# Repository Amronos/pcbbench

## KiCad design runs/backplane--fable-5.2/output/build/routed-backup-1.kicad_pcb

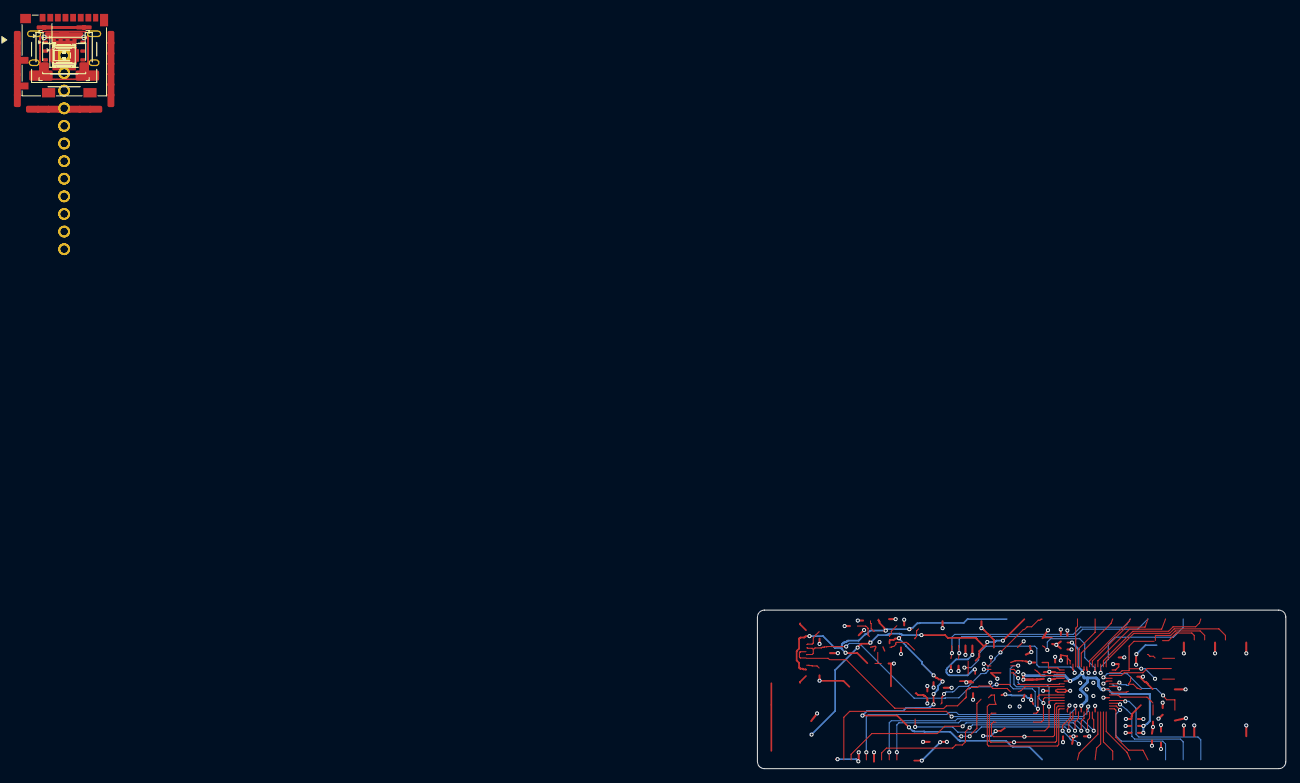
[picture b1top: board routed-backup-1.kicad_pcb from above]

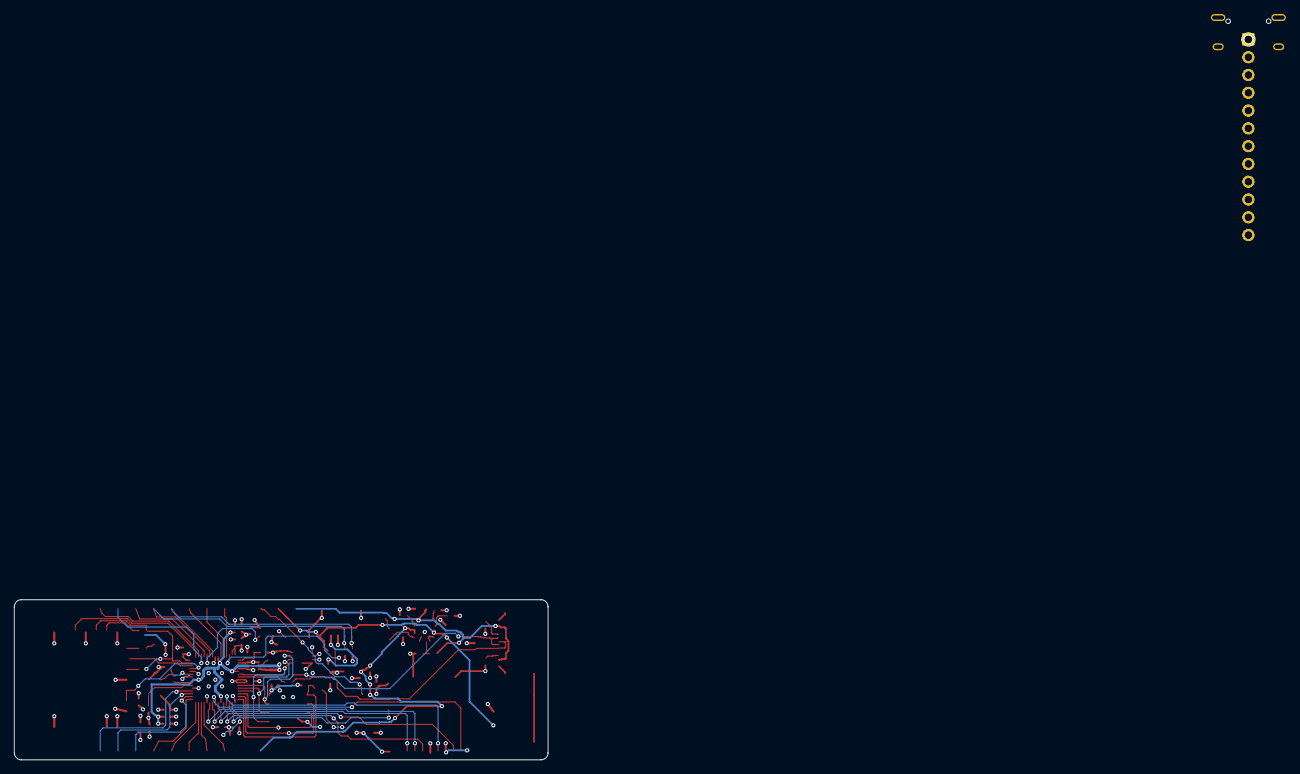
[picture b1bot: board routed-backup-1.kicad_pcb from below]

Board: 4 copper layers, 76.2 x 22.9 mm, 76 parts (3 on the bottom side), 68 nets.

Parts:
C1: 4.7uF; C_0603_1608Metric
C2, C3, C4, C28, C30: 10uF; C_0603_1608Metric
C5: 1uF; C_0402_1005Metric
C6, C7, C8, C9, C10, C11, C12, C13, C15, C16, C17, C18, C25, C26, C27, C29, C31, C32: 100nF; C_0402_1005Metric
C19, C20, C21: 4.7uF; C_0402_1005Metric
C23, C24: 15pF; C_0402_1005Metric
D1: WS2812B-2020; LED_WS2812B-2020_PLCC4_2.0x2.0mm
D2: ORANGE; LED_0603_1608Metric
D3: GREEN; LED_0603_1608Metric
J1: USB-C; USB_C_Receptacle_HRO_TYPE-C-31-M-12
J2: LiPo; JST_PH_S2B-PH-SM4-TB_1x02-1MP_P2.00mm_Horizontal
J3: Qwiic; JST_SH_SM04B-SRSS-TB_1x04-1MP_P1.00mm_Horizontal
J4: microSD; microSD_HC_Molex_104031-0811
J5: HDR_TOP; PinHeader_1x12_P2.54mm_Vertical
J6: HDR_BOT; PinHeader_1x12_P2.54mm_Vertical
L1: 3.3uH; L_Murata_DFE201610P
R1, R2: 5.1k; R_0402_1005Metric
R3, R4: 27R; R_0402_1005Metric
R5, R17, R19, R26: 10k; R_0402_1005Metric
R6: 1.5k; R_0402_1005Metric
R7: 3.0k; R_0402_1005Metric
R8, R11: 100k; R_0402_1005Metric
R9: 150k; R_0402_1005Metric
R10, R28, R29: 2.2k; R_0402_1005Metric
R12, R13: 200k; R_0402_1005Metric
R14: 33R; R_0402_1005Metric
R15, R18, R27: 1k; R_0402_1005Metric
R25: 470R; R_0402_1005Metric
SW1: BOOT; SW_SPST_B3U-1000P
SW2: RESET; SW_SPST_B3U-1000P
TP1: SWCLK; TestPoint_Pad_D1.0mm
TP2: SWDIO; TestPoint_Pad_D1.0mm
TP3: GND; TestPoint_Pad_D1.5mm
U1: RP2350A; QFN-60-1EP_7x7mm_P0.4mm_EP3.4x3.4mm
U2: W25Q128JVPIQ; WSON-8-1EP_6x5mm_P1.27mm_EP3.4x4.3mm
U3: APS6404L-3SQR-ZR; Winbond_USON-8-1EP_3x2mm_P0.5mm_EP0.2x1.6mm
U4: BQ24074RGTR; VQFN-16-1EP_3x3mm_P0.5mm_EP1.6x1.6mm
U5: TLV75733PDBVR; SOT-23-5
U6: USBLC6-2SC6; SOT-23-6
U7: RM2; RMC20452T
Y1: 12MHz; Crystal_SMD_3225-4Pin_3.2x2.5mm

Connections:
+1V1: C16.1, C17.1, C18.1, C21.1, L1.1, U1.6, U1.23, U1.39, U1.50
+3V3: C4.1, C7.1, C8.1, C9.1, C10.1, C11.1, C12.1, C13.1, C15.1, C19.1, C25.1, C26.1, C27.1, C28.1, C29.1, C30.1, C31.1, C32.1, D1.4, J3.2, J4.4, J6.1, R14.1, R17.1, R19.1, R28.1, R29.1, U1.1, U1.11, U1.20, U1.30, U1.38, U1.44, U1.45, U1.49, U1.53, U1.54, U2.8, U3.8, U5.5, U7.14, U7.16
/BAT_SENSE: C6.1, R12.2, R13.1, U1.43
/BOOT: R18.2, SW1.1
/CC1: J1.A5, R1.1
/CC2: J1.B5, R2.1
/CHG_A: D2.2, R10.2
/CHG_N: D2.1, U4.9
/EN: J5.3, R11.2, U5.3
/GP8: J6.5, U1.12
/GP9: J6.6, U1.13
/GP10: J6.7, U1.14
/GP11: J6.8, U1.15
/GP12: J6.9, U1.16
/GP13: J6.10, U1.17
/GP14: J6.11, U1.18
/GP15: J6.12, U1.19
/GP20: J5.12, U1.32
/GP21: J5.11, U1.33
/GP22: J5.10, U1.34
/GP26_A0: J5.7, U1.40
/GP27_A1: J5.6, U1.41
/GP28_A2: J5.5, U1.42
/ILIM: R6.1, U4.12
/ISET: R7.1, U4.16
/LED_A: D3.2, R27.2
/PSRAM_CS: R19.2, U1.2, U3.1
/QSPI_SCLK: U1.56, U2.6, U3.6
/QSPI_SD0: U1.57, U2.5, U3.5
/QSPI_SD1: U1.59, U2.2, U3.2
/QSPI_SD2: U1.58, U2.3, U3.3
/QSPI_SD3: U1.55, U2.7, U3.7
/QSPI_SS: R17.2, R18.1, U1.60, U2.1
/RGB_DIN: D1.3, U1.35
/RUN: SW2.1, U1.26
/SCL: J3.4, J5.8, R29.2, U1.37
/SDA: J3.3, J5.9, R28.2, U1.36
/SD_CD: J4.9, U1.3
/SD_CLK: J4.5, U1.4
/SD_CMD: J4.3, U1.5
/SD_D0: J4.7, U1.7
/SD_D1: J4.8, U1.8
/SD_D2: J4.1, U1.9
/SD_D3: J4.2, U1.10
/SWCLK: TP1.1, U1.24
/SWDIO: TP2.1, U1.25
/TS: R5.1, U4.1
/USB_DM: J1.A7, J1.B7, R4.1, U6.1, U6.6
/USB_DM_R: R4.2, U1.51
/USB_DP: J1.A6, J1.B6, R3.1, U6.3, U6.4
/USB_DP_R: R3.2, U1.52
/VBUS_DET: R8.2, R9.1, U4.6
/VREG_AVDD: C20.1, R14.2, U1.46
/VREG_LX: L1.2, U1.48
/WL_CLK: U1.31, U7.3
/WL_CS: U1.28, U7.9
/WL_D: R25.2, R26.1, U1.29, U7.5
/WL_DOUT: R25.1, U7.6
/WL_GPIO0: R27.1, U7.8
/WL_IRQ: R26.2, U7.10
/WL_ON: U1.27, U7.12, U7.13
/XIN: C23.1, U1.21, Y1.1
/XOUT: R15.1, U1.22
/XTAL_O: C24.1, R15.2, Y1.3
GND: C1.2, C2.2, C3.2, C4.2, C5.2, C6.2, C7.2, C8.2, C9.2, C10.2, C11.2, C12.2, C13.2, C15.2, C16.2, C17.2, C18.2, C19.2, C20.2, C21.2, C23.2, C24.2, C25.2, C26.2, C27.2, C28.2, C29.2, C30.2, C31.2, C32.2, D1.2, D3.1, J1.A1, J1.A12, J1.B1, J1.B12, J1.SH, J2.1, J2.MP, J3.1, J3.MP, J4.6, J4.10, J4.SH, J5.4, J6.2, J6.4, R1.2, R2.2, R5.2, R6.2, R7.2, R9.2, R13.2, SW1.2, SW2.2, TP3.1, U1.47, U1.61, U2.4, U2.9, U3.4, U3.9, U4.4, U4.5, U4.8, U4.17, U5.2, U6.2, U7.1, U7.4, U7.7, U7.11, U7.15, U7.21, Y1.2, Y1.4
VBAT: C3.1, J2.2, J5.2, R12.1, U4.2, U4.3
VBUS: C1.1, J1.A4, J1.A9, J1.B4, J1.B9, J5.1, R8.1, R10.1, U4.13, U6.5
VSYS: C2.1, C5.1, J6.3, R11.1, U4.10, U4.11, U5.1

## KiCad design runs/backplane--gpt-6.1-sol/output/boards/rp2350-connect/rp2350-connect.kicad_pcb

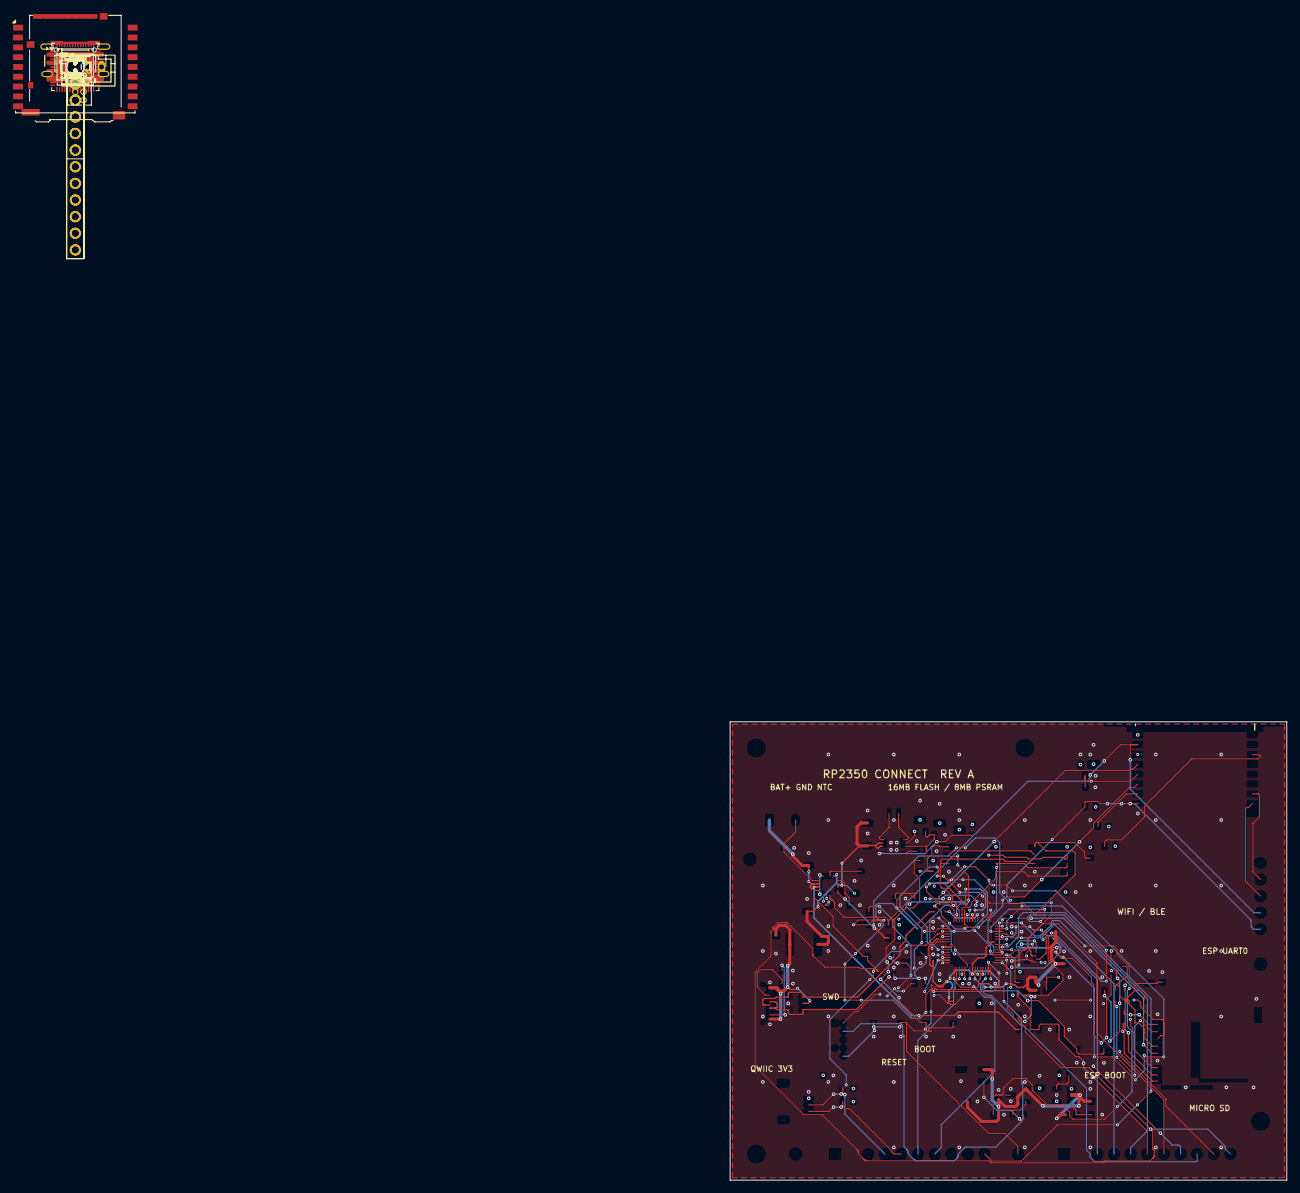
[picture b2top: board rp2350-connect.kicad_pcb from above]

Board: 6 copper layers, 85.0 x 70.0 mm, 125 parts (0 on the bottom side), 83 nets.

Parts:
C1, C2, C20, C25, C31, C33, C35, C36, C38, C39, C42, C43, C44: 100n; C_0603_1608Metric
C3, C16, C40: 4.7u; C_0805_2012Metric
C4, C22, C23, C24, C26, C27, C37, C41: 10u; C_0805_2012Metric
C5: 120p; C_0603_1608Metric
C6, C7, C8, C9, C10, C11, C12, C13, C14, C15: 100n; C_0402_1005Metric
C17, C21: 1u; C_0603_1608Metric
C18, C19: 15p; C_0402_1005Metric
C28, C29, C30, C34: 22u; C_1206_3216Metric
C32: 10p; C_0603_1608Metric
D1: 5V TVS; D_SOD-123F
D2: Addressable RGB; LED_SK6812MINI_PLCC4_3.5x3.5mm_P1.75mm
F1: 750mA resettable; Fuse_1812_4532Metric
FID1, FID2, FID3: Fiducial; Fiducial_1mm_Mask2mm
H1, H2, H3, H4: M2.5; MountingHole_2.7mm_M2.5
J1: USB-C; USB_C_Receptacle_GCT_USB4105-xx-A_16P_TopMnt_Horizontal
J2: LiPo + NTC; JST_PH_B3B-PH-K_1x03_P2.00mm_Vertical
J3: ESP UART0; PinSocket_1x06_P2.54mm_Vertical
J4: microSD SPI; microSD_HC_Hirose_DM3AT-SF-PEJM5
J5: Qwiic / STEMMA QT; JST_SH_SM04B-SRSS-TB_1x04-1MP_P1.00mm_Horizontal
J6: GPIO socket A; PinSocket_1x12_P2.54mm_Vertical
J7: GPIO socket B; PinSocket_1x12_P2.54mm_Vertical
J8: SWD; PinHeader_2x05_P1.27mm_Vertical
L1: 470nH; L_Murata_DFE201610P
L2: 1uH; L_Murata_DFE201610P
L3: 2.2uH; L_Murata_DFE201610P
R1, R2, R8, R20, R21, R27, R28, R29, R30: 10k; R_0603_1608Metric
R3: 83.5k; R_0603_1608Metric
R4, R5, R17, R18, R19, R23, R24, R25, R26, R43, R44: 100k; R_0603_1608Metric
R6: 200; R_0603_1608Metric
R7, R9: 1k; R_0603_1608Metric
R10, R11: 5.1k; R_0603_1608Metric
R12, R13: 27; R_0603_1608Metric
R14: 1.78k; R_0603_1608Metric
R15: 3.24k; R_0603_1608Metric
R16: 39k; R_0603_1608Metric
R22: 560k; R_0603_1608Metric
R31, R32, R33, R34, R35, R36: 47k; R_0603_1608Metric
R37: 33; R_0603_1608Metric
R38, R39: 4.7k; R_0603_1608Metric
R40: 976k; R_0603_1608Metric
R41: 309k; R_0603_1608Metric
R42: 330; R_0603_1608Metric
R45: 100; R_0603_1608Metric
SW1, SW2, SW3: Pushbutton; SW_SPST_PTS810
U1: RP2350A; QFN-60-1EP_7x7mm_P0.4mm_EP3.4x3.4mm
U2: 16MB QSPI; SOIC-8_5.3x5.3mm_P1.27mm
U3: 8MB PSRAM; SOIC-8_3.9x4.9mm_P1.27mm
U4: 1.1V core buck; Texas_VSON-HR-8_1.5x2mm_P0.5mm
U5: USB ESD; SOT-23-6
U6: LiPo power-path; VQFN-16-1EP_3x3mm_P0.5mm_EP1.6x1.6mm
U7: 3.3V buck-boost; Texas_S-PWSON-N10
U8: Wi-Fi + BLE; ESP32-C3-WROOM-02
U9: 5V LED boost; SOT-23-6_LED
U10: LED level buffer; SOT-23-5
U11: SD power switch; SOT-363_SC-70-6
Y1: 12MHz CL10pF; Crystal_SMD_3225-4Pin_3.2x2.5mm

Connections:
/1V1: C4.1, C5.1, C13.1, C14.1, C15.1, L1.2, R3.1, U1.6 (DVDD), U1.23 (DVDD), U1.39 (DVDD)
/3V3: C1.1, C2.1, C3.1, C6.1, C7.1, C8.1, C9.1, C10.1, C11.1, C12.1, C16.1, C28.1, C29.1, C30.1, C34.1, C35.1, C39.1, C40.1, C44.1, J3.2, J5.2, J6.1, J7.1, J8.1, L3.1, R1.2, R2.2, R5.2, R6.1, R8.2, R20.2, R21.2, R22.1, R24.2, R28.2, R29.2, R30.2, R38.2, R39.2, U1.1 (IOVDD), U1.11 (IOVDD), U1.20 (IOVDD), U1.30 (IOVDD), U1.38 (IOVDD), U1.45 (IOVDD), U1.46 (VREG_AVDD), U1.49 (VREG_VIN), U1.53 (USB_OTP_VDD), U1.54 (QSPI_IOVDD), U2.8 (VCC), U3.8 (VDD), U4.1 (EN), U4.7 (VIN), U7.9 (VOUT), U8.1 (3V3), U9.3 (EN), U9.6 (V_{IN}), U11.1 (IN)
/ADC_3V3: C17.1, R6.2, U1.44 (ADC_AVDD)
/BAT_NTC: C25.1, J2.3, U6.1 (TS)
/BB_L1: L2.1, U7.1 (L1)
/BB_L2: L2.2, U7.10 (L2)
/BB_VAUX: C31.1, U7.6 (VAUX)
/BOOT_SW: R9.2, SW2.1
/CC1: J1.A5 (CC1), R10.1
/CC2: J1.B5 (CC2), R11.1
/CHG_DISABLE: J7.11, R19.1, U1.31 (GPIO19), U6.4 (~CE)
/CHG_ILIM: R15.1, U6.12 (ILIM)
/CHG_ISET: R14.1, U6.16 (ISET)
/CHG_N: J7.7, R21.1, U1.33 (GPIO21), U6.9 (~CHG)
/CHG_TIMER: R16.1, U6.14 (TMR)
/CORE_FB: C5.2, R3.2, R4.1, U4.2 (FB)
/CORE_PG: R5.1, U4.8 (PG)
/CORE_SW: L1.1, U4.6 (SW)
/ESP_AT_CTS: U1.10 (GPIO7), U8.4 (IO5)
/ESP_AT_RTS: U1.9 (GPIO6), U8.3 (IO4)
/ESP_AT_RX: U1.7 (GPIO4), U8.5 (IO6)
/ESP_AT_TX: U1.8 (GPIO5), U8.6 (IO7)
/ESP_BOOT: J3.6, R28.1, SW3.1, U1.28 (GPIO17), U8.8 (IO9)
/ESP_EN: C36.1, J3.5, R27.1, U1.27 (GPIO16), U8.2 (EN)
/ESP_PROG_RX: J3.4, U8.11 (IO20/RXD)
/ESP_PROG_TX: J3.3, U8.12 (IO21/TXD)
/ESP_STRAP2: R30.1, U8.16 (IO2)
/ESP_STRAP8: R29.1, U8.7 (IO8)
/FLASH_CS: R1.1, R9.1, U1.60 (~QSPI_SS), U2.1 (~CS)
/GND: C1.2, C2.2, C3.2, C4.2, C6.2, C7.2, C8.2, C9.2, C10.2, C11.2, C12.2, C13.2, C14.2, C15.2, C16.2, C17.2, C18.2, C19.2, C20.2, C21.2, C22.2, C23.2, C24.2, C25.2, C26.2, C27.2, C28.2, C29.2, C30.2, C31.2, C32.2, C33.2, C34.2, C35.2, C36.2, C37.2, C38.2, C39.2, C40.2, C41.2, C42.2, C43.2, C44.2, D1.1 (A1), D2.2 (VSS), J1.A1 (GND), J1.A12 (GND), J1.B1 (GND), J1.B12 (GND), J1.SH (SHIELD), J2.2, J3.1, J4.6 (VSS), J4.10 (DET_A), J4.SH (SHIELD), J5.1, J6.2, J6.11, J7.2, J7.12, J8.3, J8.5, J8.9, R4.2, R10.2, R11.2, R14.2, R15.2, R16.2, R17.2, R18.2, R19.2, R23.2, R26.2, R27.2, R41.2, R43.2, R44.2, SW1.2, SW2.2, SW3.2, U1.47 (VREG_PGND), U1.50 (VREG_FB), U1.61 (GND), U2.4 (GND), U3.4 (VSS), U4.3 (AGND), U4.5 (PGND), U5.2 (GND), U6.8 (VSS), U6.17 (VSS), U7.4 (PS/SYNC), U7.7 (GND), U7.11 (PGND), U8.9 (GND), U8.19 (GND), U9.2 (GND), U10.1, U10.3 (GND), U11.2 (GND), Y1.2 (G), Y1.4 (G)
/GP12: J6.6, U1.16 (GPIO12)
/GP13: J6.7, U1.17 (GPIO13)
/GP14: J6.8, U1.18 (GPIO14)
/GP15: J6.9, U1.19 (GPIO15)
/GP25: J6.10, U1.37 (GPIO25)
/GP27: J7.3, U1.41 (GPIO27/ADC1)
/GP28: J7.4, U1.42 (GPIO28/ADC2)
/GP29: J7.5, U1.43 (GPIO29/ADC3)
/I2C_SCL: J5.4, J6.5, R39.1, U1.5 (GPIO3)
/I2C_SDA: J5.3, J6.4, R38.1, U1.4 (GPIO2)
/LED_5V: C41.1, C42.1, C43.1, D2.4 (VDD), R40.1, U9.5 (V_{OUT}), U10.5 (VCC)
/LED_FB: R40.2, R41.1, U9.4 (V_{FB})
/LED_SW: L3.2, U9.1 (SW)
/MAIN_FB: C32.1, R22.2, R23.1, U7.8 (FB)
/MAIN_PG: R24.1, U7.5 (PG)
/PSRAM_CS: R2.1, U1.2 (GPIO0), U3.1 (~CE)
/QSPI_CLK: U1.56 (QSPI_SCLK), U2.6 (CLK), U3.6 (SCLK)
/QSPI_D0: U1.57 (QSPI_SD0), U2.5 (DI/IO_{0}), U3.5 (SI/SIO0)
/QSPI_D1: U1.59 (QSPI_SD1), U2.2 (DO/IO_{1}), U3.2 (SO/SIO1)
/QSPI_D2: U1.58 (QSPI_SD2), U2.3 (~WP/IO_{2}), U3.3 (SIO2)
/QSPI_D3: U1.55 (QSPI_SD3), U2.7 (~HOLD/~RESET/IO_{3}), U3.7 (SIO3)
/RGB_5V_DATA: R42.1, U10.4
/RGB_DATA: R43.1, U1.35 (GPIO23), U10.2
/RGB_DIN: D2.3 (DIN), R42.2
/RUN: C20.1, J6.12, J8.10, R8.1, SW1.1, U1.26 (RUN)
/SD_3V3: C37.1, C38.1, J4.4 (VDD), R31.2, R32.2, R33.2, R34.2, R35.2, R36.2, R45.2, U11.6 (OUT)
/SD_CLK: J4.5 (CLK), R37.2
/SD_CLK_DRV: R37.1, U1.14 (GPIO10)
/SD_CS: J4.2 (DAT3/CD), R31.1, U1.13 (GPIO9)
/SD_DAT1: J4.8 (DAT1), R34.1
/SD_DAT2: J4.1 (DAT2), R35.1
/SD_DET_N: J4.9 (DET_B), R36.1, U1.36 (GPIO24)
/SD_MISO: J4.7 (DAT0), R33.1, U1.12 (GPIO8)
/SD_MOSI: J4.3 (CMD), R32.1, U1.15 (GPIO11)
/SD_PWR_EN: J6.3, R44.1, U1.3 (GPIO1), U11.3 (ON)
/SD_QOD: R45.1, U11.5 (QOD)
/SWCLK: J8.4, U1.24 (SWCLK)
/SWDIO: J8.2, U1.25 (SWDIO)
/USB_DM: J1.A7 (D-), J1.B7 (D-), R12.1, U5.1 (I/O1), U5.6 (I/O1)
/USB_DM_MCU: R12.2, U1.51 (USB_DM)
/USB_DP: J1.A6 (D+), J1.B6 (D+), R13.1, U5.3 (I/O2), U5.4 (I/O2)
/USB_DP_MCU: R13.2, U1.52 (USB_DP)
/USB_EN1: J7.9, R17.1, U1.29 (GPIO18), U6.6 (EN1)
/USB_EN2: J7.10, R18.1, U1.32 (GPIO20), U6.5 (EN2)
/USB_PGOOD_N: J7.8, R20.1, U1.34 (GPIO22), U6.7 (~PGOOD)
/VBAT: C22.1, J2.1, R25.1, U6.2 (BAT), U6.3 (BAT)
/VBAT_ADC: C33.1, J7.6, R25.2, R26.1, U1.40 (GPIO26/ADC0)
/VBUS: C21.1, C24.1, F1.2, U6.13 (IN)
/VBUS_RAW: D1.2 (A2), F1.1, J1.A4 (VBUS), J1.A9 (VBUS), J1.B4 (VBUS), J1.B9 (VBUS), U5.5 (VBUS)
/VSYS: C23.1, C26.1, C27.1, U6.10 (OUT), U6.11 (OUT), U7.2 (VIN), U7.3 (EN)
/XIN: C18.1, U1.21 (XIN), Y1.1
/XOUT: C19.1, R7.2, Y1.3
/XOUT_DRV: R7.1, U1.22 (XOUT)

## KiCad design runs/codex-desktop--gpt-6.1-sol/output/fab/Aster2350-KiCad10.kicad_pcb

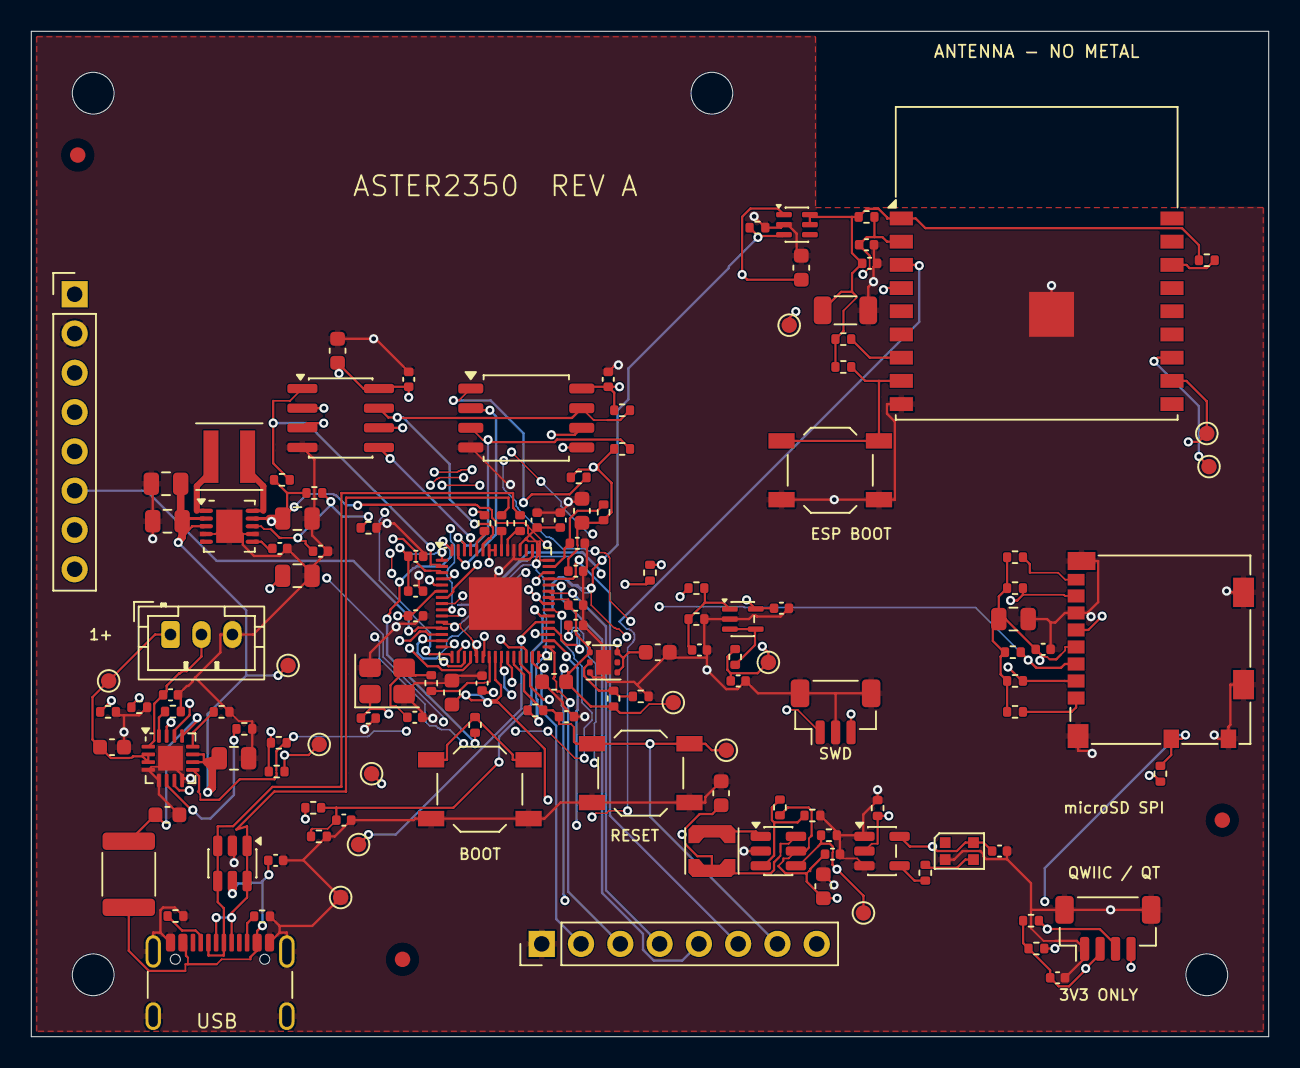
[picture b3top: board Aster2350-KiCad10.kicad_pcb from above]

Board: 4 copper layers, 80.0 x 65.0 mm, 141 parts (0 on the bottom side), 84 nets.

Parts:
C1, C2: 15p; Capacitor_SMD__C_0402_1005Metric
C3, C4, C6, C7, C8, C9, C10, C11, C12, C13, C15, C17, C20, C21, C25, C30, C32, C33, C34, C35, C36, C39, C41, C42, C45, C46: 100n; Capacitor_SMD__C_0402_1005Metric
C5, C16, C18, C22, C37: 1u; Capacitor_SMD__C_0603_1608Metric
C14, C19, C24, C43, C44: 4.7u; Capacitor_SMD__C_0603_1608Metric
C23, C26, C27, C40: 10u; Capacitor_SMD__C_0805_2012Metric
C28, C29: 22u; Capacitor_SMD__C_0805_2012Metric
C31: 10p; Capacitor_SMD__C_0402_1005Metric
C38: 47u; Capacitor_SMD__C_1206_3216Metric
D1: WS2812B-2020; LED_SMD__LED_WS2812B-2020_PLCC4_2.0x2.0mm
F1: 500mA PTC; Fuse__Fuse_1812_4532Metric
FID1, FID2, FID3: Fiducial
H1, H2, H3, H4: MountingHole
J1: USB-C; Connector_USB__USB_C_Receptacle_GCT_USB4105-xx-A_16P_TopMnt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
J2: LiPo + NTC; Connector_JST__JST_PH_B3B-PH-K_1x03_P2.00mm_Vertical
J3: microSD; Connector_Card__microSD_HC_Molex_104031-0811
J4: Qwiic / STEMMA QT; Connector_JST__JST_SH_BM04B-SRSS-TB_1x04-1MP_P1.00mm_Vertic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
J5: SWD; Connector_JST__JST_SH_BM03B-SRSS-TB_1x03-1MP_P1.00mm_Vertic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
J6: GPIO A; Connector_PinHeader_2.54mm__PinHeader_1x08_P2.54mm_Vertical
J7: GPIO B; Connector_PinHeader_2.54mm__PinHeader_1x08_P2.54mm_Vertical
L1: 1.5uH; Inductor_SMD__L_Coilcraft_XxL4020
L2: 10uH; Inductor_SMD__L_Coilcraft_LPS3010
R1, R11, R27: 1k; Resistor_SMD__R_0402_1005Metric
R2, R7, R41: 33; Resistor_SMD__R_0402_1005Metric
R3, R4, R5, R6: 4.7k; Resistor_SMD__R_0402_1005Metric
R8, R9, R10, R31, R32, R33, R34, R35, R36, R37, R38, R39: 10k; Resistor_SMD__R_0402_1005Metric
R12, R13, R28: 5.1k; Resistor_SMD__R_0402_1005Metric
R14, R15: 27; Resistor_SMD__R_0402_1005Metric
R16: 3.57k; Resistor_SMD__R_0402_1005Metric
R17: 3.24k; Resistor_SMD__R_0402_1005Metric
R18: 49.9k; Resistor_SMD__R_0402_1005Metric
R19, R21, R22, R40: 3.3k; Resistor_SMD__R_0402_1005Metric
R20, R24, R25, R26, R30, R45, R46, R47: 100k; Resistor_SMD__R_0402_1005Metric
R23: 562k; Resistor_SMD__R_0402_1005Metric
R29: 6.8k; Resistor_SMD__R_0402_1005Metric
R42, R43: 2.2k; Resistor_SMD__R_0402_1005Metric
R44: 536k; Resistor_SMD__R_0402_1005Metric
R48: 330; Resistor_SMD__R_0402_1005Metric
SW1: BOOTSEL; Button_Switch_SMD__SW_SPST_TL3342
SW2: RESET; Button_Switch_SMD__SW_SPST_TL3342
SW3: ESP BOOT; Button_Switch_SMD__SW_SPST_TL3342
TP1: GND; TestPoint__TestPoint_Pad_D1.0mm
TP2: VSYS; TestPoint__TestPoint_Pad_D1.0mm
TP3: +3V3; TestPoint__TestPoint_Pad_D1.0mm
TP4: +1V1; TestPoint__TestPoint_Pad_D1.0mm
TP5: BAT; TestPoint__TestPoint_Pad_D1.0mm
TP6: BAT_ADC; TestPoint__TestPoint_Pad_D1.0mm
TP7: RADIO_RX; TestPoint__TestPoint_Pad_D1.0mm
TP8: RADIO_TX; TestPoint__TestPoint_Pad_D1.0mm
TP9: ESP_EN; TestPoint__TestPoint_Pad_D1.0mm
TP10: POWER_GOOD_N; TestPoint__TestPoint_Pad_D1.0mm
TP11: USB_500MA; TestPoint__TestPoint_Pad_D1.0mm
TP12: RUN; TestPoint__TestPoint_Pad_D1.0mm
TP13: RGB_ENABLE; TestPoint__TestPoint_Pad_D1.0mm
U1: RP2350A; Package_DFN_QFN__QFN-60-1EP_7x7mm_P0.4mm_EP3.4x3.4mm
U2: W25Q128JVSIQ; Package_SO__SOIC-8_5.3x5.3mm_P1.27mm
U3: APS6404L-3SQR-SN; Package_SO__SOIC-8_3.9x4.9mm_P1.27mm
U4: TLV75801PDRVR; Package_SON__WSON-6-1EP_2x2mm_P0.65mm_EP1x1.6mm
U5: USBLC6-2SC6; Package_TO_SOT_SMD__SOT-23-6
U6: BQ24074RGTR; Package_DFN_QFN__VQFN-16-1EP_3x3mm_P0.5mm_EP1.6x1.6mm
U7: TPS63060DSCR; Package_SON__Texas_S-PWSON-N10
U8: TLV9001IDCKR; Package_TO_SOT_SMD__SOT-353_SC-70-5
U9: ESP32-C3-WROOM-02-N4; RF_Module__ESP32-C3-WROOM-02
U10: TPS22919DCKR; Package_TO_SOT_SMD__SOT-363_SC-70-6
U11: TLV61046ADBVR; Package_TO_SOT_SMD__SOT-23-6
U12: SN74AHCT1G125DBVR; Package_TO_SOT_SMD__SOT-23-5
Y1: 12MHz; Crystal__Crystal_SMD_3225-4Pin_3.2x2.5mm

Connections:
+1V1: C13.1, C14.1, C15.1, C19.1, R8.1, TP4.1, U1.6 (DVDD), U1.23 (DVDD), U1.39 (DVDD), U4.1 (OUT)
+3V3: C3.1, C4.1, C5.1, C6.1, C7.1, C8.1, C9.1, C10.1, C11.1, C12.1, C16.1, C18.1, C28.1, C29.1, C33.1, C37.1, C40.1, C41.1, C42.1, C43.1, J3.4 (VDD), J4.2, J6.1, J7.8, L2.1, R3.1, R4.1, R5.1, R6.1, R7.1, R10.1, R21.1, R22.1, R23.1, R35.1, R36.1, R37.1, R38.1, R39.1, R40.1, R42.1, R43.1, TP3.1, U1.1 (IOVDD), U1.11 (IOVDD), U1.20 (IOVDD), U1.30 (IOVDD), U1.38 (IOVDD), U1.45 (IOVDD), U1.46 (VREG_AVDD), U1.49 (VREG_VIN), U1.53 (USB_OTP_VDD), U1.54 (QSPI_IOVDD), U2.8 (VCC), U3.8 (VDD), U4.4 (EN), U4.6 (IN), U7.9 (VOUT), U8.5 (V+), U10.1 (IN), U11.6 (VIN)
+3V3_ADC: C17.1, R7.2, U1.44 (ADC_AVDD)
+3V3_RF: C38.1, C39.1, R31.1, R32.1, R33.1, R34.1, U9.1 (3V3), U10.5 (QOD), U10.6 (OUT)
+5V_RGB: C44.1, C45.1, C46.1, D1.4 (VDD), R44.1, U11.5 (VOUT), U12.5 (VCC)
BAT: C24.1, J2.1, R25.1, TP5.1, U6.2 (BAT), U6.3 (BAT)
BAT_ADC: C34.1, R27.2, TP6.1, U1.43 (GPIO29/ADC3)
BAT_BUFFER: R27.1, U8.3 (-), U8.4
BAT_DIV: C32.1, R25.2, R26.1, U8.1 (+)
BAT_NTC: C25.1, J2.2, U6.1 (TS)
BOOT_GND: R11.2, SW1.1
BUCK_FB: C31.1, R23.2, R24.1, U7.8 (FB)
BUCK_L1: L1.1, U7.1 (L1)
BUCK_L2: L1.2, U7.10 (L2)
BUCK_VAUX: C30.1, U7.6 (VAUX)
CC1: J1.A5 (CC1), R12.1
CC2: J1.B5 (CC2), R13.1
CHARGE_N: R21.2, U1.37 (GPIO25), U6.9 (~CHG)
CHG_ILIM: R17.1, U6.12 (ILIM)
CHG_ISET: R16.1, U6.16 (ISET)
CHG_ITERM: R19.1, U6.15 (ITERM)
CHG_TMR: R18.1, U6.14 (TMR)
CORE_FB: R8.2, R9.1, U4.2 (FB)
ESP_BOOT: R33.2, SW3.1, U9.8 (IO9)
ESP_EN: C36.1, R31.2, TP9.1, U9.2 (EN)
ESP_STRAP2: R34.2, U9.16 (IO2)
ESP_STRAP8: R32.2, U9.7 (IO8)
FLASH_CS: R3.2, R11.1, U1.60 (~QSPI_SS), U2.1 (~CS)
GND: C1.2, C2.2, C3.2, C4.2, C5.2, C6.2, C7.2, C8.2, C9.2, C10.2, C11.2, C12.2, C13.2, C14.2, C15.2, C16.2, C17.2, C18.2, C19.2, C20.2, C21.2, C22.2, C23.2, C24.2, C25.2, C26.2, C27.2, C28.2, C29.2, C30.2, C31.2, C32.2, C33.2, C34.2, C35.2, C36.2, C37.2, C38.2, C39.2, C40.2, C41.2, C42.2, C43.2, C44.2, C45.2, C46.2, D1.2 (VSS), J1.A1 (GND), J1.A12 (GND), J1.B1 (GND), J1.B12 (GND), J1.SH (SHIELD), J2.3, J3.6 (VSS), J3.10 (DET_A), J3.SH (SHIELD), J4.1, J4.MP, J5.2, J5.MP, J6.2, J7.1, R9.2, R12.2, R13.2, R16.2, R17.2, R18.2, R19.2, R20.2, R24.2, R26.2, R29.2, R30.2, R45.2, R46.2, R47.2, SW1.2, SW2.2, SW3.2, TP1.1, U1.47 (VREG_PGND), U1.50 (VREG_FB), U1.61 (GND), U2.4 (GND), U3.4 (VSS), U4.3 (GND), U4.7 (GND), U5.2 (GND), U6.4 (~CE), U6.5 (EN2), U6.8 (VSS), U6.17 (VSS), U7.4 (PS/SYNC), U7.7 (GND), U7.11 (PGND), U8.2 (V-), U9.9 (GND), U9.19 (GND), U10.2 (GND), U11.2 (GND), U12.1, U12.3 (GND), Y1.2 (G), Y1.4 (G)
GPIO1: J6.3, U1.3 (GPIO1)
GPIO2: J6.4, U1.4 (GPIO2)
GPIO3: J6.5, U1.5 (GPIO3)
GPIO8: J6.6, U1.12 (GPIO8)
GPIO9: J6.7, U1.13 (GPIO9)
GPIO15: J6.8, U1.19 (GPIO15)
GPIO18: J7.2, U1.29 (GPIO18)
GPIO19: J7.3, U1.31 (GPIO19)
GPIO26_ADC0: J7.4, U1.40 (GPIO26/ADC0)
GPIO27_ADC1: J7.5, U1.41 (GPIO27/ADC1)
GPIO28_ADC2: J7.6, U1.42 (GPIO28/ADC2)
I2C_SCL: J4.4, R43.2, U1.33 (GPIO21)
I2C_SDA: J4.3, R42.2, U1.32 (GPIO20)
POWER_GOOD_N: R22.2, TP10.1, U6.7 (~PGOOD)
PSRAM_CS: R4.2, U1.2 (GPIO0), U3.1 (~CE)
QSPI_CLK: R2.2, U2.6 (CLK), U3.6 (SCLK)
QSPI_CLK_SRC: R2.1, U1.56 (QSPI_SCLK)
QSPI_D0: U1.57 (QSPI_SD0), U2.5 (DI/IO_{0}), U3.5 (SI/SIO0)
QSPI_D1: U1.59 (QSPI_SD1), U2.2 (DO/IO_{1}), U3.2 (SO/SIO1)
QSPI_D2: R5.2, U1.58 (QSPI_SD2), U2.3 (~WP/IO_{2}), U3.3 (SIO2)
QSPI_D3: R6.2, U1.55 (QSPI_SD3), U2.7 (~HOLD/~RESET/IO_{3}), U3.7 (SIO3)
RADIO_CTS: U1.10 (GPIO7), U9.3 (IO4)
RADIO_POWER: R30.1, U1.34 (GPIO22), U10.3 (ON)
RADIO_RTS: U1.9 (GPIO6), U9.4 (IO5)
RADIO_RX: TP7.1, U1.7 (GPIO4), U9.11 (IO20/RXD)
RADIO_TX: TP8.1, U1.8 (GPIO5), U9.12 (IO21/TXD)
RGB_DATA: R47.1, U1.27 (GPIO16), U12.2
RGB_DIN: D1.3 (DIN), R48.2
RGB_DOUT_BUF: R48.1, U12.4
RGB_ENABLE: R46.1, TP13.1, U1.28 (GPIO17), U11.4 (EN)
RGB_FB: R44.2, R45.1, U11.3 (FB)
RGB_SW: L2.2, U11.1 (SW)
RUN: C20.1, J7.7, R10.2, SW2.1, TP12.1, U1.26 (RUN)
SD_CS: J3.2 (DAT3/CD), R35.2, U1.17 (GPIO13)
SD_DAT1: J3.8 (DAT1), R38.2
SD_DAT2: J3.1 (DAT2), R39.2
SD_DETECT: J3.9 (DET_B), R40.2, U1.18 (GPIO14)
SD_MISO: J3.7 (DAT0), R36.2, U1.16 (GPIO12)
SD_MOSI: J3.3 (CMD), R37.2, U1.15 (GPIO11)
SD_SCK: J3.5 (CLK), R41.2
SD_SCK_SRC: R41.1, U1.14 (GPIO10)
SWCLK: J5.1, U1.24 (SWCLK)
SWDIO: J5.3, U1.25 (SWDIO)
USB_500MA: R20.1, TP11.1, U1.35 (GPIO23), U6.6 (EN1)
USB_DM: J1.A7 (D-), J1.B7 (D-), R15.1, U5.3 (I/O2), U5.4 (I/O2)
USB_DM_MCU: R15.2, U1.51 (USB_DM)
USB_DP: J1.A6 (D+), J1.B6 (D+), R14.1, U5.1 (I/O1), U5.6 (I/O1)
USB_DP_MCU: R14.2, U1.52 (USB_DP)
USB_VBUS: C21.1, F1.1, J1.A4 (VBUS), J1.A9 (VBUS), J1.B4 (VBUS), J1.B9 (VBUS), U5.5 (VBUS)
VBUS: C22.1, F1.2, R28.1, U6.13 (IN)
VBUS_DETECT: C35.1, R28.2, R29.1, U1.36 (GPIO24)
VSYS: C23.1, C26.1, C27.1, TP2.1, U6.10 (OUT), U6.11 (OUT), U7.2 (VIN), U7.3 (EN)
XIN: C1.1, U1.21 (XIN), Y1.1
XOUT: R1.1, U1.22 (XOUT)
XTAL_OUT: C2.1, R1.2, Y1.3

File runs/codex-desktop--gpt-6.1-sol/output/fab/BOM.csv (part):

Item,References,Quantity,Value,Manufacturer,MPN,Footprint,Assembly,Side,Populate,Description
1,C1 C2,2,15p,Murata,GRM1555C1H150JA01D,Aster:Capacitor_SMD__C_0402_1005Metric,SMT,Top,Yes,"15 pF, 50 V, C0G, 5%, 0402"
2,C3 C4 C6 C7 C8 C9 C10 C11 C12 C13 C15 C17 C20 C21 C25 C30 C32 C33 C34 C35 C36 C39 C41 C42 C45 C46,26,100n,Murata,GRM155R71C104KA88D,Aster:Capacitor_SMD__C_0402_1005Metric,SMT,Top,Yes,"100 nF, 16 V, X7R, 10%, 0402"
3,C5 C16 C18 C22 C37,5,1u,Murata,GRM188R71C105KA12D,Aster:Capacitor_SMD__C_0603_1608Metric,SMT,Top,Yes,"1 uF, 16 V, X7R, 10%, 0603"
4,C14 C19 C24 C43 C44,5,4.7u,Murata,GRM188R61A475KE15D,Aster:Capacitor_SMD__C_0603_1608Metric,SMT,Top,Yes,"4.7 uF, 10 V, X5R, 10%, 0603"
5,C23 C26 C27 C40,4,10u,Murata,GRM21BR61C106KE15L,Aster:Capacitor_SMD__C_0805_2012Metric,SMT,Top,Yes,"10 uF, 16 V, X5R, 10%, 0805"
6,C28 C29,2,22u,Murata,GRM21BR61A226ME44L,Aster:Capacitor_SMD__C_0805_2012Metric,SMT,Top,Yes,"22 uF, 10 V, X5R, 20%, 0805"
7,C31,1,10p,Murata,GRM1555C1H100JA01D,Aster:Capacitor_SMD__C_0402_1005Metric,SMT,Top,Yes,"10 pF, 50 V, C0G, 5%, 0402"
8,C38,1,47u,Murata,GRM31CR61A476ME15L,Aster:Capacitor_SMD__C_1206_3216Metric,SMT,Top,Yes,"47 uF, 10 V, X5R, 20%, 1206"
9,D1,1,WS2812B-2020,Worldsemi,WS2812B-2020,Aster:LED_SMD__LED_WS2812B-2020_PLCC4_2.0x2.0mm,SMT,Top,Yes,"Addressable RGB LED, 800 kbit/s, 5 V supply, GRB; observe pin-1 orientation"
10,F1,1,500mA PTC,Bourns,MF-MSMF050-2,Aster:Fuse__Fuse_1812_4532Metric,SMT,Top,Yes,"500 mA hold resettable fuse, 15 V max, 1812"
11,J1,1,USB-C,GCT,USB4105-GF-A,Aster:Connector_USB__USB_C_Receptacle_GCT_USB4105-xx-A_16P_TopMnt_Horizontal,SMT,Top,Yes,"USB 2.0 device, both plug orientations; plated shell slots"
12,J2,1,LiPo + NTC,JST,B3B-PH-K-S(LF)(SN),Aster:Connector_JST__JST_PH_B3B-PH-K_1x03_P2.00mm_Vertical,THT,Top,Yes,"Protected 1S 4.2 V LiPo, >=500 mAh, 10 kohm 3435 K pack thermistor; pin 1=BAT+, 2=NTC, 3=GND"
13,J3,1,microSD,Molex,104031-0811,Aster:Connector_Card__microSD_HC_Molex_104031-0811,SMT,Top,Yes,"Push-pull microSD socket with card detect; SPI mode, 3.3 V only"
14,J4,1,Qwiic / STEMMA QT,JST,BM04B-SRSS-TB(LF)(SN),Aster:Connector_JST__JST_SH_BM04B-SRSS-TB_1x04-1MP_P1.00mm_Vertical,SMT,Top,Yes,"1.0 mm JST SH; GND,3V3,SDA,SCL; 3.3 V peripherals, 100 mA total external budget"
15,J5,1,SWD,JST,BM03B-SRSS-TB(LF)(SN),Aster:Connector_JST__JST_SH_BM03B-SRSS-TB_1x03-1MP_P1.00mm_Vertical,SMT,Top,Yes,"Raspberry Pi Debug Probe pinout: SWCLK,GND,SWDIO; target is self-powered"
16,J6,1,GPIO A,Wurth Elektronik,61300811121,Aster:Connector_PinHeader_2.54mm__PinHeader_1x08_P2.54mm_Vertical,THT,Top,Yes,Factory installed 1x8 2.54 mm male header; 3.3 V logic only
17,J7,1,GPIO B,Wurth Elektronik,61300811121,Aster:Connector_PinHeader_2.54mm__PinHeader_1x08_P2.54mm_Vertical,THT,Top,Yes,Factory installed 1x8 2.54 mm male header; ADC0/1/2 available
18,L1,1,1.5uH,Coilcraft,XFL4020-152MEC,Aster:Inductor_SMD__L_Coilcraft_XxL4020,SMT,Top,Yes,"1.5 uH, 20%, shielded, Isat=4.4 A, DCR=14.4 milliohm"
19,L2,1,10uH,Coilcraft,LPS3010-103MLC,Aster:Inductor_SMD__L_Coilcraft_LPS3010,SMT,Top,Yes,"10 uH, 20%, shielded, >1 A saturation current"
20,R1 R11 R27,3,1k,Yageo,RC0402FR-071KL,Aster:Resistor_SMD__R_0402_1005Metric,SMT,Top,Yes,"1%, 0402, 62.5 mW; zero-ohm link only where specified"
21,R2 R7 R41,3,33,Yageo,RC0402FR-0733RL,Aster:Resistor_SMD__R_0402_1005Metric,SMT,Top,Yes,"1%, 0402, 62.5 mW; zero-ohm link only where specified"
22,R3 R4 R5 R6,4,4.7k,Yageo,RC0402FR-074K7L,Aster:Resistor_SMD__R_0402_1005Metric,SMT,Top,Yes,"1%, 0402, 62.5 mW; zero-ohm link only where specified"
23,R8 R9 R10 R31 R32 R33 R34 R35 R36 R37 R38 R39,12,10k,Yageo,RC0402FR-0710KL,Aster:Resistor_SMD__R_0402_1005Metric,SMT,Top,Yes,"1%, 0402, 62.5 mW; zero-ohm link only where specified"
24,R12 R13 R28,3,5.1k,Yageo,RC0402FR-075K1L,Aster:Resistor_SMD__R_0402_1005Metric,SMT,Top,Yes,"1%, 0402, 62.5 mW; zero-ohm link only where specified"
25,R14 R15,2,27,Yageo,RC0402FR-0727RL,Aster:Resistor_SMD__R_0402_1005Metric,SMT,Top,Yes,"1%, 0402, 62.5 mW; zero-ohm link only where specified"
26,R16,1,3.57k,Yageo,RC0402FR-073K57L,Aster:Resistor_SMD__R_0402_1005Metric,SMT,Top,Yes,"1%, 0402, 62.5 mW; zero-ohm link only where specified"
27,R17,1,3.24k,Yageo,RC0402FR-073K24L,Aster:Resistor_SMD__R_0402_1005Metric,SMT,Top,Yes,"1%, 0402, 62.5 mW; zero-ohm link only where specified"
28,R18,1,49.9k,Yageo,RC0402FR-0749K9L,Aster:Resistor_SMD__R_0402_1005Metric,SMT,Top,Yes,"1%, 0402, 62.5 mW; zero-ohm link only where specified"
29,R19 R21 R22 R40,4,3.3k,Yageo,RC0402FR-073K3L,Aster:Resistor_SMD__R_0402_1005Metric,SMT,Top,Yes,"1%, 0402, 62.5 mW; zero-ohm link only where specified"
30,R20 R24 R25 R26 R30 R45 R46 R47,8,100k,Yageo,RC0402FR-07100KL,Aster:Resistor_SMD__R_0402_1005Metric,SMT,Top,Yes,"1%, 0402, 62.5 mW; zero-ohm link only where specified"
31,R23,1,562k,Yageo,RC0402FR-07562KL,Aster:Resistor_SMD__R_0402_1005Metric,SMT,Top,Yes,"1%, 0402, 62.5 mW; zero-ohm link only where specified"
32,R29,1,6.8k,Yageo,RC0402FR-076K8L,Aster:Resistor_SMD__R_0402_1005Metric,SMT,Top,Yes,"1%, 0402, 62.5 mW; zero-ohm link only where specified"
33,R42 R43,2,2.2k,Yageo,RC0402FR-072K2L,Aster:Resistor_SMD__R_0402_1005Metric,SMT,Top,Yes,"1%, 0402, 62.5 mW; zero-ohm link only where specified"
34,R44,1,536k,Yageo,RC0402FR-07536KL,Aster:Resistor_SMD__R_0402_1005Metric,SMT,Top,Yes,"1%, 0402, 62.5 mW; zero-ohm link only where specified"
35,R48,1,330,Yageo,RC0402FR-07330RL,Aster:Resistor_SMD__R_0402_1005Metric,SMT,Top,Yes,"1%, 0402, 62.5 mW; zero-ohm link only where specified"
36,SW1,1,BOOTSEL,E-Switch,TL3342F160QG,Aster:Button_Switch_SMD__SW_SPST_TL3342,SMT,Top,Yes,Hold while applying power or RESET for ROM USB mass-storage boot
37,SW2,1,RESET,E-Switch,TL3342F160QG,Aster:Button_Switch_SMD__SW_SPST_TL3342,SMT,Top,Yes,RP2350 reset button
38,SW3,1,ESP BOOT,E-Switch,TL3342F160QG,Aster:Button_Switch_SMD__SW_SPST_TL3342,SMT,Top,Yes,Hold low through radio power-on to flash the ESP32-C3 ROM UART bootloader
39,U1,1,RP2350A,Raspberry Pi,RP2350A,Aster:Package_DFN_QFN__QFN-60-1EP_7x7mm_P0.4mm_EP3.4x3.4mm,SMT,Top,Yes,"QFN60, external 1.1 V core supply; VREG_FB grounded, LX deliberately open"
40,U2,1,W25Q128JVSIQ,Winbond,W25Q128JVSIQ,Aster:Package_SO__SOIC-8_5.3x5.3mm_P1.27mm,SMT,Top,Yes,"16 MiB QSPI NOR, 3 V, 208 mil SOIC8"
41,U3,1,APS6404L-3SQR-SN,AP Memory,APS6404L-3SQR-SN,Aster:Package_SO__SOIC-8_3.9x4.9mm_P1.27mm,SMT,Top,Yes,"8 MiB 3.3 V QSPI PSRAM, 150 mil SOP8; NOT a 1.8 V variant"
42,U4,1,TLV75801PDRVR,Texas Instruments,TLV75801PDRVR,Aster:Package_SON__WSON-6-1EP_2x2mm_P0.65mm_EP1x1.6mm,SMT,Top,Yes,"500 mA adjustable LDO, 0.55 V reference, 1.100 V nominal core; WSON thermal pad grounded"
43,U5,1,USBLC6-2SC6,STMicroelectronics,USBLC6-2SC6,Aster:Package_TO_SOT_SMD__SOT-23-6,SMT,Top,Yes,USB low-capacitance ESD array; pin-pairs are the same net
44,U6,1,BQ24074RGTR,Texas Instruments,BQ24074RGTR,Aster:Package_DFN_QFN__VQFN-16-1EP_3x3mm_P0.5mm_EP1.6x1.6mm,SMT,Top,Yes,"4.2 V single-cell LiPo charger; OUT=4.4 V USB power path, 250 mA maximum charging"
45,U7,1,TPS63060DSCR,Texas Instruments,TPS63060DSCR,Aster:Package_SON__Texas_S-PWSON-N10,SMT,Top,Yes,"2.25 A switch buck-boost, 3.310 V nominal output; PS/SYNC low enables power-save"
46,U8,1,TLV9001IDCKR,Texas Instruments,TLV9001IDCKR,Aster:Package_TO_SOT_SMD__SOT-353_SC-70-5,SMT,Top,Yes,RRIO voltage follower prevents RP2350 GPIO leakage loading battery divider
47,U9,1,ESP32-C3-WROOM-02-N4,Espressif,ESP32-C3-WROOM-02-N4,Aster:RF_Module__ESP32-C3-WROOM-02,SMT,Top,Yes,"2.4 GHz Wi-Fi b/g/n + Bluetooth LE 5, 4 MiB flash, PCB antenna; factory firmware must be programmed"
48,U10,1,TPS22919DCKR,Texas Instruments,TPS22919DCKR,Aster:Package_TO_SOT_SMD__SOT-363_SC-70-6,SMT,Top,Yes,"1.5 A load switch, quick-output-discharge tied to switched rail; off by default"
49,U11,1,TLV61046ADBVR,Texas Instruments,TLV61046ADBVR,Aster:Package_TO_SOT_SMD__SOT-23-6,SMT,Top,Yes,Dedicated switched 5.06 V RGB boost rail; off by default
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
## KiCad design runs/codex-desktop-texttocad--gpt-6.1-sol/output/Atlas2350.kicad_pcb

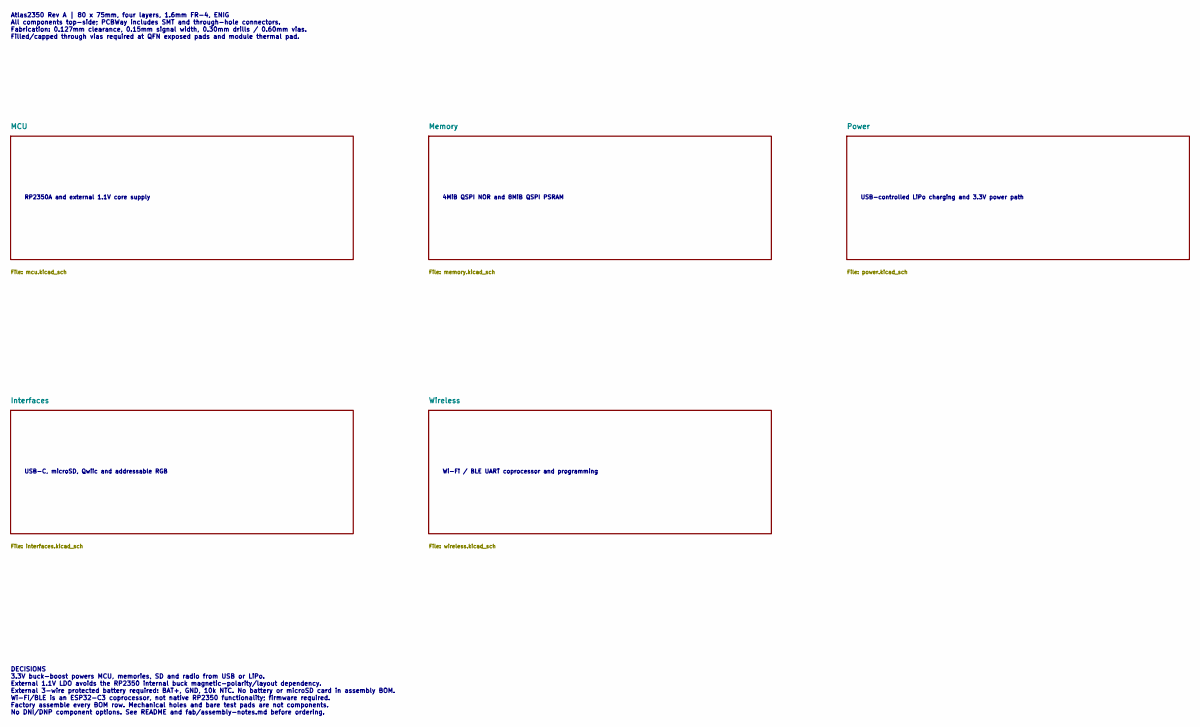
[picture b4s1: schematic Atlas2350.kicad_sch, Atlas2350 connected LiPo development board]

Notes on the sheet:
RP2350A and external 1.1V core supply
4MiB QSPI NOR and 8MiB QSPI PSRAM
USB-controlled LiPo charging and 3.3V power path
USB-C, microSD, Qwiic and addressable RGB
Wi-Fi / BLE UART coprocessor and programming
Atlas2350 Rev A | 80 x 75mm, four layers, 1.6mm FR-4, ENIG All components top-side; PCBWay includes SMT and through-hole connectors. Fabrication: 0.127mm clearance, 0.15mm signal width, 0.30mm drills / 0.60mm vias. Filled/capped through vias required at QFN exposed pads and module thermal pad.
DECISIONS 3.3V buck-boost powers MCU, memories, SD and radio from USB or LiPo. External 1.1V LDO avoids the RP2350 internal buck magnetic-polarity/layout dependency. External 3-wire protected battery required: BAT+, GND, 10k NTC. No battery or microSD card in assembly BOM. Wi-Fi/BLE is an ESP32-C3 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
